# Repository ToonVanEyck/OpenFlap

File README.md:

# OpenFlap

!!! warning

    🚨 This is still a work in progress. Using the the code and files in this repository to create your own display is not recommended at the moment! 🚨

The OpenFlap project aims to create a open source, affordable split-flap display for the makers and tinkerers of the world.
This repository houses all the required files to build, program and modify your very own split-flap display. 

[**Read the Docs**](https://toonvaneyck.github.io/OpenFlap/)

## Specifications

- 48 Flaps per module.
- 49mm x 70mm Character size.
- Stackable & Chainable.
- Daisy chain communication.
- Per module configuration & calibration.
- HTTP API available.
- Modular design.
- 3D printable parts.

## Design Philosophy

The OpenFlap system is designed to be modular and expandable, using common components and manufacturing techniques such as 3D printing and printed circuit boards.

The OpenFlap system uses DC geared motors instead of traditional stepper motors. This simplifies the mechanical design and reduces the cost of the system. Additionally this reduces the power consumption of the system and allows the split-flap display to rotate faster than the traditionally used stepper motors. 

The OpenFlap system is designed to be as plug and play as possible. The system is able to determine it's own display size, and should only require calibration once.

The OpenFlap system has a web interface that allows local control of the display. The web interface uses a HTTP API to communicate with the display, this API also allows external services to communicate with the display. No authentication or security measures are implemented at the moment.

The OpenFlap system can connect to your local WiFi network or host it's own network.

## I want to ...

[... know more about how the OpenFlap system works.](docs/architecture.md)

[... build my own OpenFlap display.](todo)

[... contribute to the OpenFlap project.](docs/developing.md)

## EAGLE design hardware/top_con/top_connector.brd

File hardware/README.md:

Hardware
========

All PCB's are designed in Fusion 360, the source files can be accessed an copied through the links below:

Module
------
### Side Panel
- [side panel: Electronic Design](https://a360.co/3LnqHKp)
- [side panel: PCB](https://a360.co/3OHfgiH)
- [side panel: Schematic](https://a360.co/3EQSoZI)
- [side panel: 3D](https://a360.co/3vO3oD5)

### Flap
- [flap profile: PCB](https://a360.co/3KnExLN)
- [flap profile: 3D](https://a360.co/3KmTDAU)

### Encoder Wheel
- [wheel: PCB](https://a360.co/3LnqMxH)
- [wheel: 3D](https://a360.co/37JMbTs)

Top-Con
-------
- [top-con: Electronic Design](https://a360.co/3KmcPPo)
- [top-con: PCB](https://a360.co/36RFDl1)
- [top-con: Schematic](https://a360.co/3Mybp5H)
- [top-con: 3D](https://a360.co/3ETtb0O)

Controller
----------
- [controller: Electronic Design](https://a360.co/3vmdjzr)
- [controller: PCB](https://a360.co/3LnqmHD)
- [controller: Schematic](https://a360.co/3xTXOSp)
- [controller: 3D](https://a360.co/3rY5W0q)

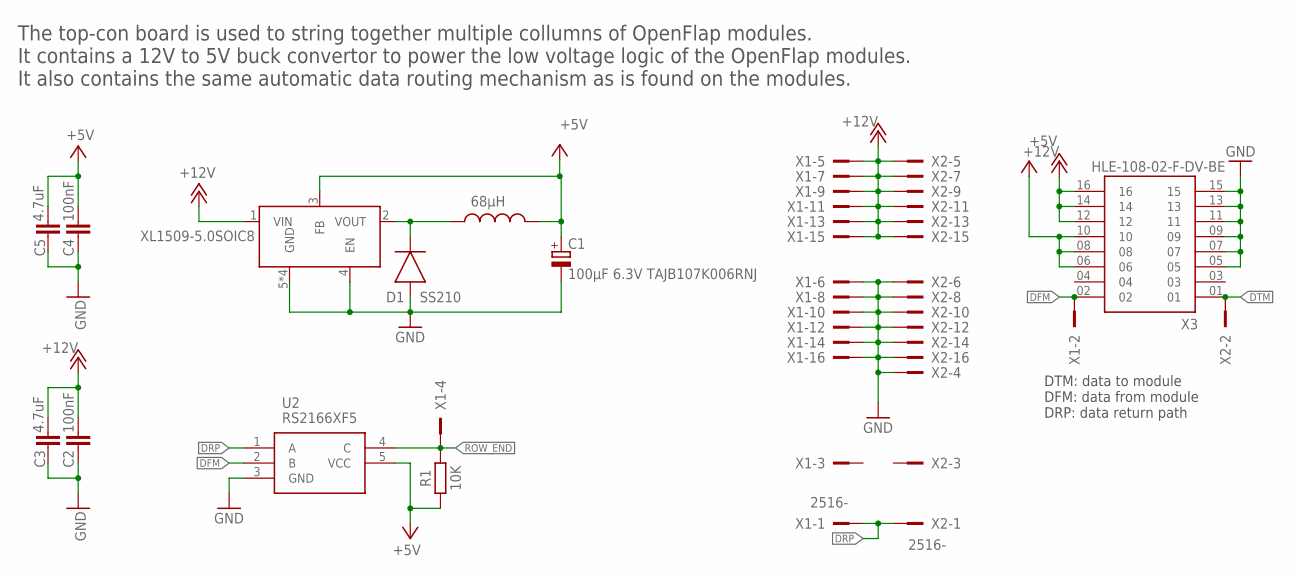
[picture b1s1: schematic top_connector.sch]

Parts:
C1: 100µF 6.3V TAJB107K006RNJ; CAPMP3528X210N
C2, C4: 100nF; CAPC2012X110
C3, C5: 4.7uF; CAPC2012X110
D1: SS210; DIOM5226X290N
L1: SWPA6045S680MT; LVS606028-100M-N
R1: 10K; RESC2012X65
U1: XL1509-5.0SOIC8; SOIC8
U2: RS2166XF5; SOT95P280X145-5N
X1, X2: 2516-; PAK100/2500-16
X3: HLE-108-02-F-DV-BE; SAMTEC_HLE-108-02-F-DV-BE

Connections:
+5V: C1.1 (+), C4.1, C5.1, L1.P$2, R1.1, U1.3 (FB), U2.5 (VCC), X3.06, X3.08, X3.10
+12V: C2.1, C3.1, U1.1 (VIN), X1.5, X1.7, X1.9, X1.11, X1.13, X1.15, X2.5, X2.7, X2.9, X2.11, X2.13, X2.15, X3.12, X3.14, X3.16
DFM: U2.2 (B), X1.2, X3.02
DRP: U2.1 (A), X1.1, X2.1
DTM: X2.2, X3.01
GND: C1.2 (-), C2.2, C3.2, C4.2, C5.2, D1.2 (A), U1.4 (EN), U1.5 (GND), U1.6 (GND), U1.7 (GND), U1.8 (GND), U2.3 (GND), X1.6, X1.8, X1.10, X1.12, X1.14, X1.16, X2.4, X2.6, X2.8, X2.10, X2.12, X2.14, X2.16, X3.05, X3.07, X3.09, X3.11, X3.13, X3.15
unnamed: D1.1 (C), L1.P$1, U1.2 (VOUT)
ROW_END: R1.2, U2.4 (C), X1.4

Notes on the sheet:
DTM: data to module DFM: data from module DRP: data return path
68µH
The top-con board is used to string together multiple collumns of OpenFlap modules. It contains a 12V to 5V buck convertor to power the low voltage logic of the OpenFlap modules. It also contains the same automatic data routing mechanism as is found on the modules.

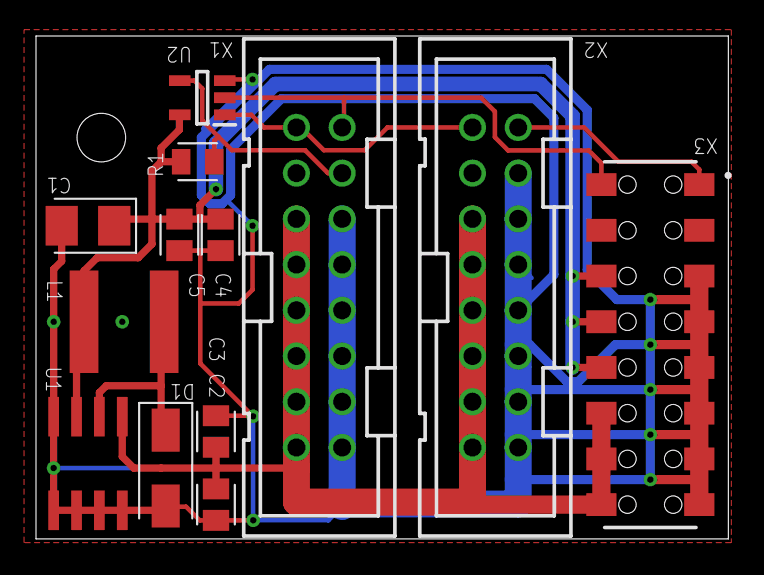
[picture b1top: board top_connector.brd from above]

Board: 2 copper layers, 38.5 x 27.9 mm, 13 parts (0 on the bottom side), 8 nets.

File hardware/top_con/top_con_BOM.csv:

Comment,Designator,Footprint,JLCPCB Part #（optional）
100µF 6.3V TAJB107K006RNJ,C1,C-POL_TANTALUM-1411(3528-METRIC),C16133
100nF,C2,C_CHIP-0805(2012-METRIC),
4.7uF,C3,C_CHIP-0805(2012-METRIC),
100nF,C4,C_CHIP-0805(2012-METRIC),
4.7uF,C5,C_CHIP-0805(2012-METRIC),
SS210,D1,DIODEDO-214AC(SMA),C14996
SWPA6045S680MT,L1,LVS606028-100M-N,C53663
10K,R1,R_CHIP-0805(2012-METRIC),
XL1509-5.0SOIC8,U1,XL1509-5.0SOIC8,C61063
SN74LVC1G66DBVR,U2,SOT23-5,C5375974
2516-,X1,2516-,
2516-,X2,2516-,
HLE-108-02-F-DV-BE,X3,HLE-108-02-F-DV-BE,

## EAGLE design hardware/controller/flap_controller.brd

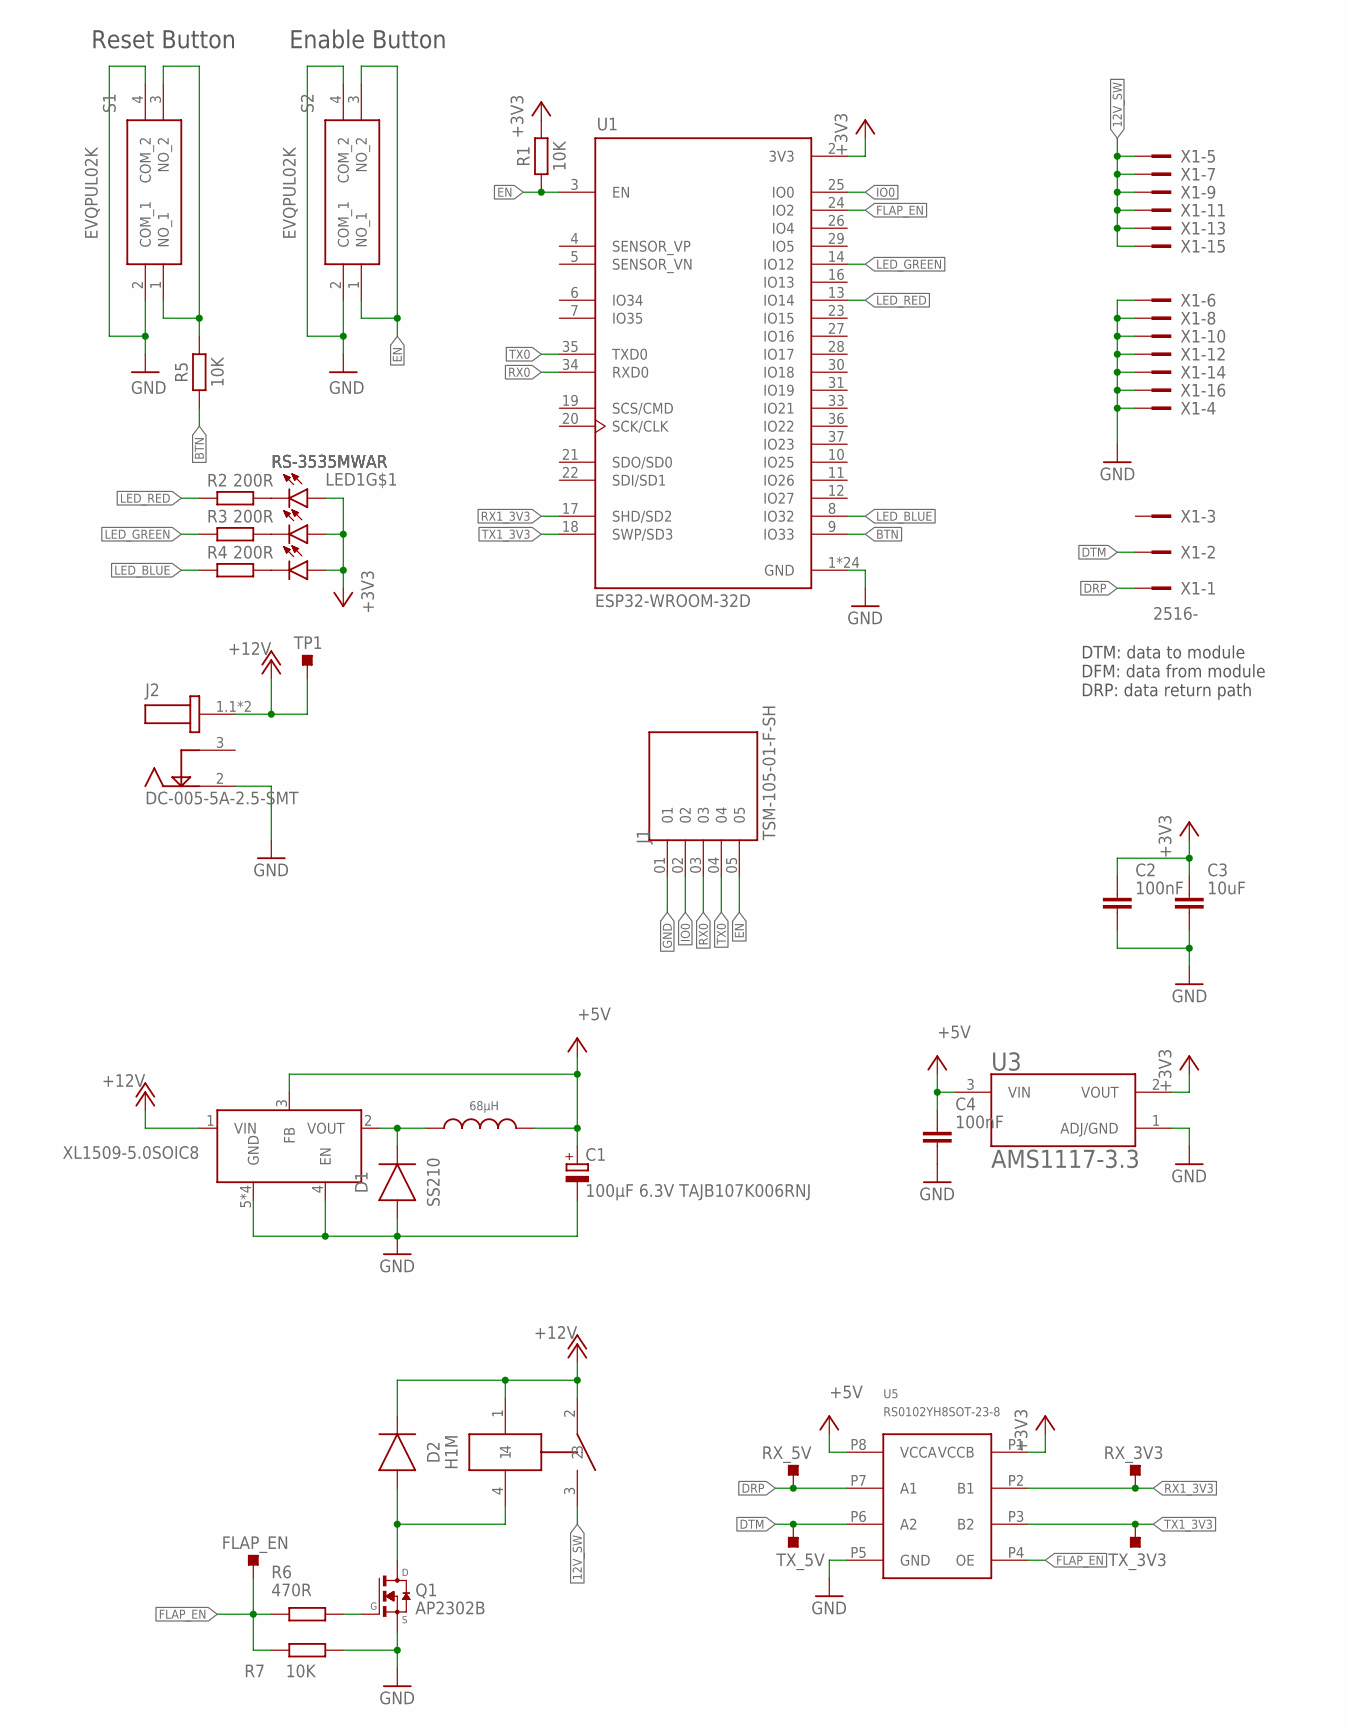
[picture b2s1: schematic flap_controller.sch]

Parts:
C1: 100µF 6.3V TAJB107K006RNJ; CAPMP3528X210N
C2, C4: 100nF; CAPC2012X110
C3: 10uF; CAPC2012X110
D1: SS210; DIOM5226X290N
D2: H1M; SODFL3718X115
FLAP_EN: TESTPOINT_TPS-PAD-036; TESTPOINT_PAD-036
J1: TSM-105-01-F-SH; SAMTEC_TSM-105-01-F-SH
J2: DC-005-5A-2.5-SMT; GCT_DCJ200-05-A-XX-X_REVA
K1: G5NB-1A-E DC12; G5NB-1A-EDC12
L1: SWPA6045S680MT; LVS606028-100M-N
LED1: RS-3535MWAR
Q1: AP2302B; TRANSISTOR-FET_SOT23
R1, R5, R7: 10K; RESC2012X65
R2, R3, R4: 200R; RESC2012X65
R6: 470R; RESC2012X65
RX_3V3, RX_5V: TESTPOINT_TPS-PAD-036; TESTPOINT_PAD-036
S1, S2: EVQPUL02K
TP1: TESTPOINT_TPS-SMD-10SN; TESTPOINT_SMD-10SN
TX_3V3, TX_5V: TESTPOINT_TPS-PAD-036; TESTPOINT_PAD-036
U1: ESP32-WROOM-32D; MODULE_ESP32-WROOM-32D
U2: XL1509-5.0SOIC8; SOIC8
U3: AMS1117-3.3; SOT229P700X180-4N
U5: RS0102YH8SOT-23-8; SOT-23-8
X1: 2516-; PAK100/2500-16

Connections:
12V_SW: K1.3, X1.5, X1.7, X1.9, X1.11, X1.13, X1.15
+3V3: C2.1, C3.1, LED1.B_A (A), LED1.G_A (A), LED1.R_A (A), R1.2, U1.2 (3V3), U3.2 (VOUT), U5.P1 (VCCB)
+5V: C1.1 (+), C4.1, L1.P$2, U2.3 (FB), U3.3 (VIN), U5.P8 (VCCA)
+12V: D2.1 (C), J2.1.1 (1), J2.1.2 (1), K1.1, K1.2, TP1.TP, U2.1 (VIN)
BTN: R5.1, U1.9 (IO33)
DRP: RX_5V.1, U5.P7 (A1), X1.1
DTM: TX_5V.1, U5.P6 (A2), X1.2
EN: J1.05, R1.1, S2.1 (NO_1), S2.3 (NO_2), U1.3 (EN)
FLAP_EN: FLAP_EN.1, R6.1, R7.1, U1.24 (IO2), U5.P4 (OE)
GND: C1.2 (-), C2.2, C3.2, C4.2, D1.2 (A), J1.01, J2.2, Q1.2 (S), R7.2, S1.2 (COM_1), S1.4 (COM_2), S2.2 (COM_1), S2.4 (COM_2), U1.1 (GND), U1.15 (GND), U1.38 (GND), U1.39_1 (GND), U1.39_2 (GND), U1.39_3 (GND), U1.39_4 (GND), U1.39_5 (GND), U1.39_6 (GND), U1.39_7 (GND), U1.39_8 (GND), U1.39_9 (GND), U1.39_10 (GND), U1.39_11 (GND), U1.39_12 (GND), U1.39_13 (GND), U1.39_14 (GND), U1.39_15 (GND), U1.39_16 (GND), U1.39_17 (GND), U1.39_18 (GND), U1.39_19 (GND), U1.39_20 (GND), U1.39_21 (GND), U2.4 (EN), U2.5 (GND), U2.6 (GND), U2.7 (GND), U2.8 (GND), U3.1 (ADJ/GND), U5.P5 (GND), X1.4, X1.6, X1.8, X1.10, X1.12, X1.14, X1.16
IO0: J1.02, U1.25 (IO0)
LED_BLUE: R4.2, U1.8 (IO32)
LED_GREEN: R3.2, U1.14 (IO12)
LED_RED: R2.2, U1.13 (IO14)
unnamed: D1.1 (C), L1.P$1, U2.2 (VOUT)
unnamed: LED1.B_K (C), R2.1
unnamed: LED1.G_K (C), R3.1
unnamed: LED1.R_K (C), R4.1
unnamed: D2.2 (A), K1.4, Q1.3 (D)
unnamed: Q1.1 (G), R6.2
unnamed: R5.2, S1.1 (NO_1), S1.3 (NO_2)
RX0: J1.03, U1.34 (RXD0)
RX1_3V3: RX_3V3.1, U1.17 (SHD/SD2), U5.P2 (B1)
TX0: J1.04, U1.35 (TXD0)
TX1_3V3: TX_3V3.1, U1.18 (SWP/SD3), U5.P3 (B2)

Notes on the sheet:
DTM: data to module DFM: data from module DRP: data return path
Reset Button
68µH
Enable Button

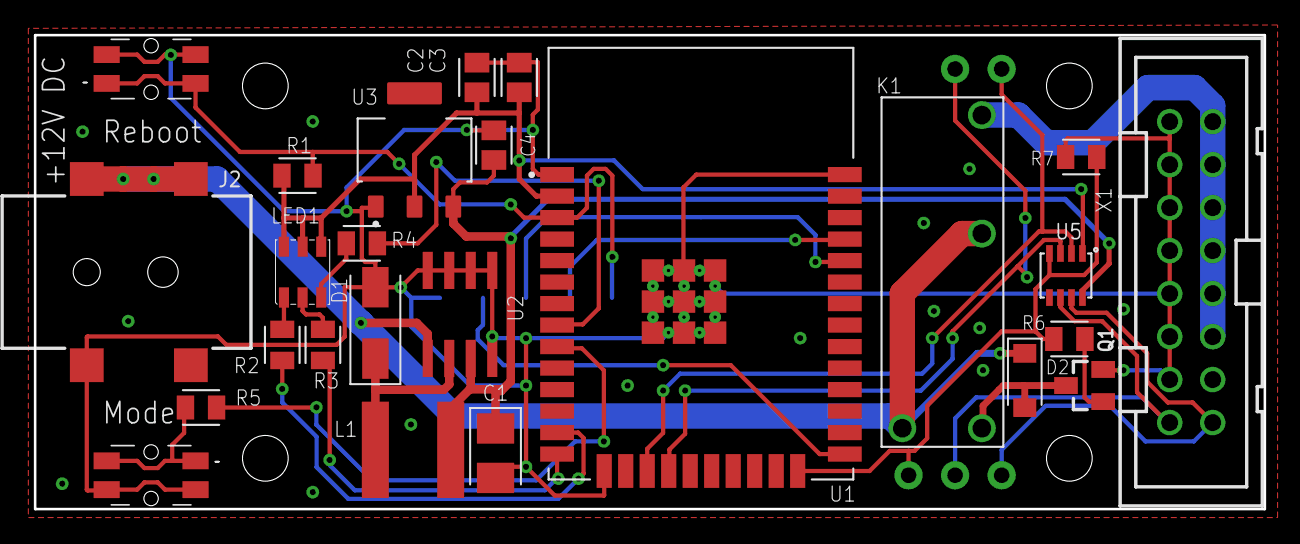
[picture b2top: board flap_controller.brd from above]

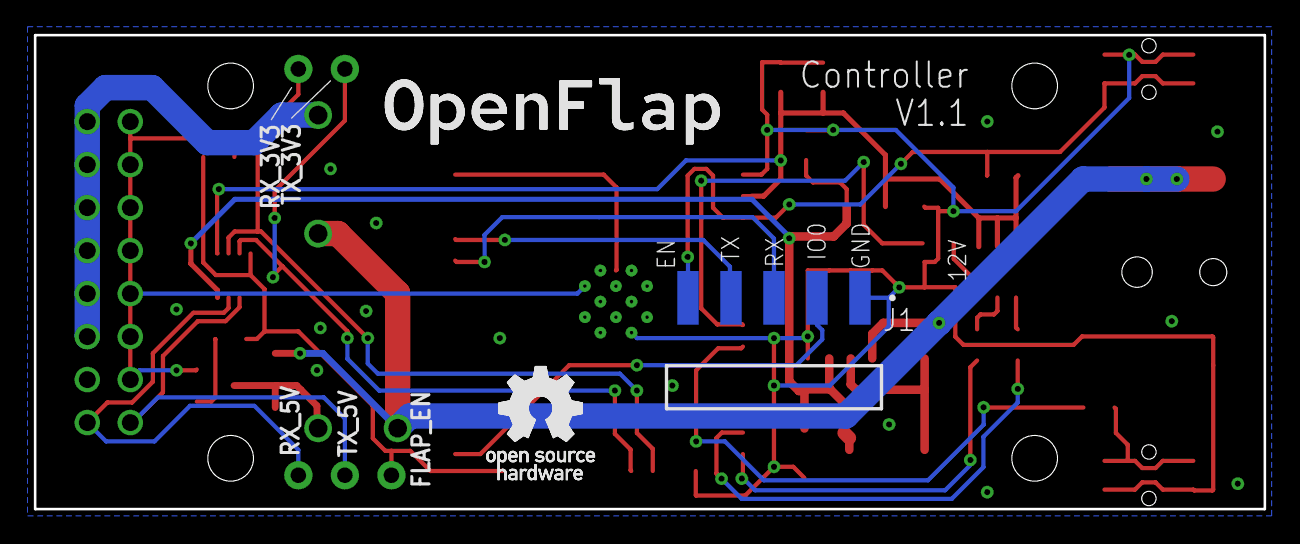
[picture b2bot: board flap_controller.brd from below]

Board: 2 copper layers, 72.6 x 28.0 mm, 32 parts (7 on the bottom side), 25 nets.

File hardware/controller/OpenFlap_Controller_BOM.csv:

Comment,Designator,Footprint,JLCPCB Part #（optional）
100nF,"C2, C4",C_CHIP-0805(2012-METRIC),C49678
TAJB107K006RNJ,C1,C-POL_TANTALUM-1411(3528-METRIC),C16133
10uF,C3,C_CHIP-0805(2012-METRIC),C15850
10K,"R1, R5, R7",R_CHIP-0805(2012-METRIC),C17414
200R,"R2, R3, R4",,C17540
2516-,X1,2516-,C3406
AMS1117-3.3,U3,AMS1117-3.3,C6186
DC-005-5A-2.5-SMT,J2,DCJ200-05-A-XX-X_REVA,C319133
ESP32-WROOM-32D,U1,ESP32-WROOM-32D,C529578
EVQPUL02K,"S1, S2",EVQPUL02K,C79175
G5NB-1A-E DC12,K1,G5NB-1A-EDC12,C225714
RS-3535MWAR,LED1,RS-3535MWAR,C110402
RS0102YH8,U5,RS0102YH8SOT-23-8,C783414
SS210,D1,DIODEDO-214AC(SMA),C14996
SWPA6045S680MT,L1,LVS606028-100M-N,C53663
TSM-105-01-F-SH,J1,TSM-105-01-F-SH,
XL1509-5.0,U2,SOIC8,C2902368
AP2302B,Q1,SOT23,C406812
H1M,D2,SODFL3718X115,C698680

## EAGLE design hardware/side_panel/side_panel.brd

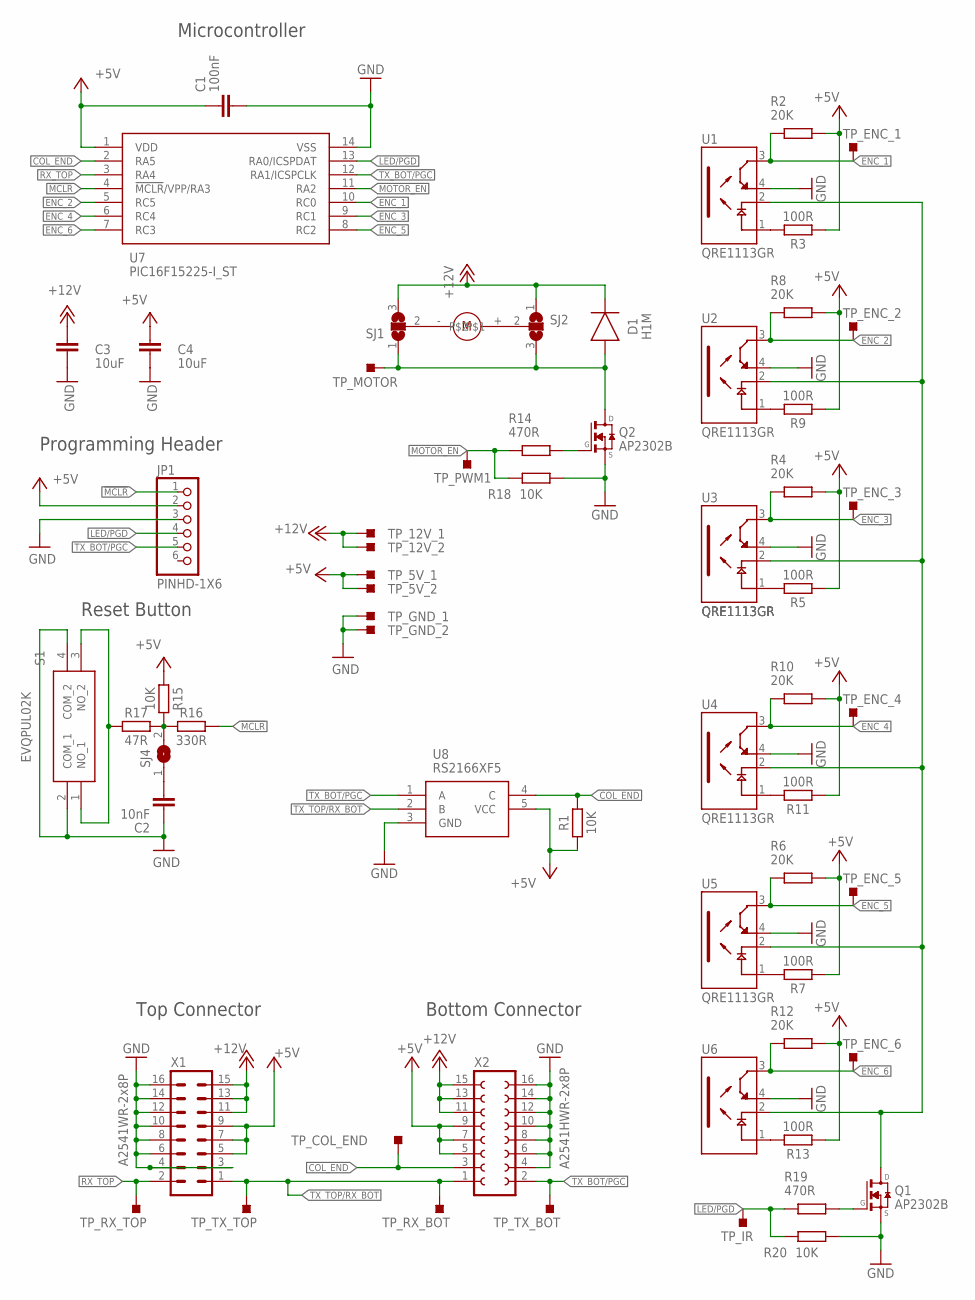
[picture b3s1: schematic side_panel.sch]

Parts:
C1: 100nF; CAPC2012X110
C2: 10nF; CAPC2012X110
C3, C4: 10uF; C0805
D1: H1M; SODFL3718X115
JP1: PINHD-1X6; 1X06
M1: GA12-N20
Q1, Q2: AP2302B; TRANSISTOR-FET_SOT23
R1, R15, R18, R20: 10K; RESC2012X65
R2, R4, R6, R8, R10, R12: 20K; RESC2012X65
R3, R5, R7, R9, R11, R13: 100R; RESC2012X65
R14, R19: 470R; RESC2012X65
R16: 330R; RESC2012X65
R17: 47R; RESC2012X65
S1: EVQPUL02K
SJ1, SJ2: SJ2W; SJ_2
SJ4: SJ
TP_5V_1, TP_5V_2, TP_12V_1, TP_12V_2: TESTPOINT_TPS-PAD-036; TESTPOINT_PAD-036
TP_COL_END: TESTPOINT_TPS-PAD-036; TESTPOINT_PAD-036
TP_ENC_1, TP_ENC_2, TP_ENC_3, TP_ENC_4, TP_ENC_5, TP_ENC_6: TESTPOINT_TPS-PAD-036; TESTPOINT_PAD-036
TP_GND_1, TP_GND_2: TESTPOINT_TPS-PAD-036; TESTPOINT_PAD-036
TP_IR: TESTPOINT_TPS-PAD-036; TESTPOINT_PAD-036
TP_MOTOR: TESTPOINT_TPS-PAD-036; TESTPOINT_PAD-036
TP_PWM1: TESTPOINT_TPS-PAD-036; TESTPOINT_PAD-036
TP_RX_BOT: TESTPOINT_TPS-PAD-036; TESTPOINT_PAD-036
TP_RX_TOP: TESTPOINT_TPS-PAD-036; TESTPOINT_PAD-036
TP_TX_BOT: TESTPOINT_TPS-PAD-036; TESTPOINT_PAD-036
TP_TX_TOP: TESTPOINT_TPS-PAD-036; TESTPOINT_PAD-036
U1, U2, U3, U4, U5, U6: QRE1113GR; SOIC180P460X187-4N
U7: PIC16F15225-I_ST; SOP65P640X120-14N
U8: RS2166XF5; SOT95P280X145-5N
X1: A2541WR-2x8P; MA08-2W
X2: A2541HWR-2x8P; FE08-2W

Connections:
!MCLR: JP1.1, R16.2, U7.4 (!MCLR!/VPP/RA3)
+5V: C1.1, C4.1, JP1.2, R1.1, R2.2, R3.1, R4.2, R5.1, R6.2, R7.1, R8.2, R9.1, R10.2, R11.1, R12.2, R13.1, R15.1, TP_5V_1.1, TP_5V_2.1, U7.1 (VDD), U8.5 (VCC), X1.5, X1.7, X1.9, X2.5, X2.7, X2.9
+12V: C3.1, D1.1 (C), SJ1.3, SJ2.1, TP_12V_1.1, TP_12V_2.1, X1.11, X1.13, X1.15, X2.11, X2.13, X2.15
COL_END: R1.2, TP_COL_END.1, U7.2 (RA5), U8.4 (C), X2.3
ENC_1: R2.1, TP_ENC_1.1, U1.3 (CT), U7.10 (RC0)
ENC_2: R8.1, TP_ENC_2.1, U2.3 (CT), U7.5 (RC5)
ENC_3: R4.1, TP_ENC_3.1, U3.3 (CT), U7.9 (RC1)
ENC_4: R10.1, TP_ENC_4.1, U4.3 (CT), U7.6 (RC4)
ENC_5: R6.1, TP_ENC_5.1, U5.3 (CT), U7.8 (RC2)
ENC_6: R12.1, TP_ENC_6.1, U6.3 (CT), U7.7 (RC3)
GND: C1.2, C2.1, C3.2, C4.2, JP1.3, Q1.2 (S), Q2.2 (S), R18.2, R20.2, S1.2 (COM_1), S1.4 (COM_2), TP_GND_1.1, TP_GND_2.1, U1.4 (ET), U2.4 (ET), U3.4 (ET), U4.4 (ET), U5.4 (ET), U6.4 (ET), U7.14 (VSS), U8.3 (GND), X1.3, X1.4, X1.6, X1.8, X1.10, X1.12, X1.14, X1.16, X2.4, X2.6, X2.8, X2.10, X2.12, X2.14, X2.16
LED/PGD: JP1.4, R19.1, R20.1, TP_IR.1, U7.13 (RA0/ICSPDAT)
MOTOR_EN: R14.1, R18.1, TP_PWM1.1, U7.11 (RA2)
unnamed: M1.-, SJ1.2
unnamed: M1.+, SJ2.2
unnamed: D1.2 (A), Q2.3 (D), SJ1.1, SJ2.3, TP_MOTOR.1
unnamed: R3.2, U1.1 (A)
unnamed: Q2.1 (G), R14.2
unnamed: R5.2, U3.1 (A)
unnamed: Q1.3 (D), U1.2 (C), U2.2 (C), U3.2 (C), U4.2 (C), U5.2 (C), U6.2 (C)
unnamed: R7.2, U5.1 (A)
unnamed: Q1.1 (G), R19.2
unnamed: R9.2, U2.1 (A)
unnamed: R11.2, U4.1 (A)
unnamed: R13.2, U6.1 (A)
unnamed: C2.2, SJ4.1
unnamed: R15.2, R16.1, R17.2, SJ4.2
unnamed: R17.1, S1.1 (NO_1), S1.3 (NO_2)
RX_TOP: TP_RX_TOP.1, U7.3 (RA4), X1.2
TX_BOT/PGC: JP1.5, TP_TX_BOT.1, U7.12 (RA1/ICSPCLK), U8.1 (A), X2.2
TX_TOP/RX_BOT: TP_RX_BOT.1, TP_TX_TOP.1, U8.2 (B), X1.1, X2.1

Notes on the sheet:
Top Connector
Bottom Connector
Reset Button
Programming Header
Microcontroller

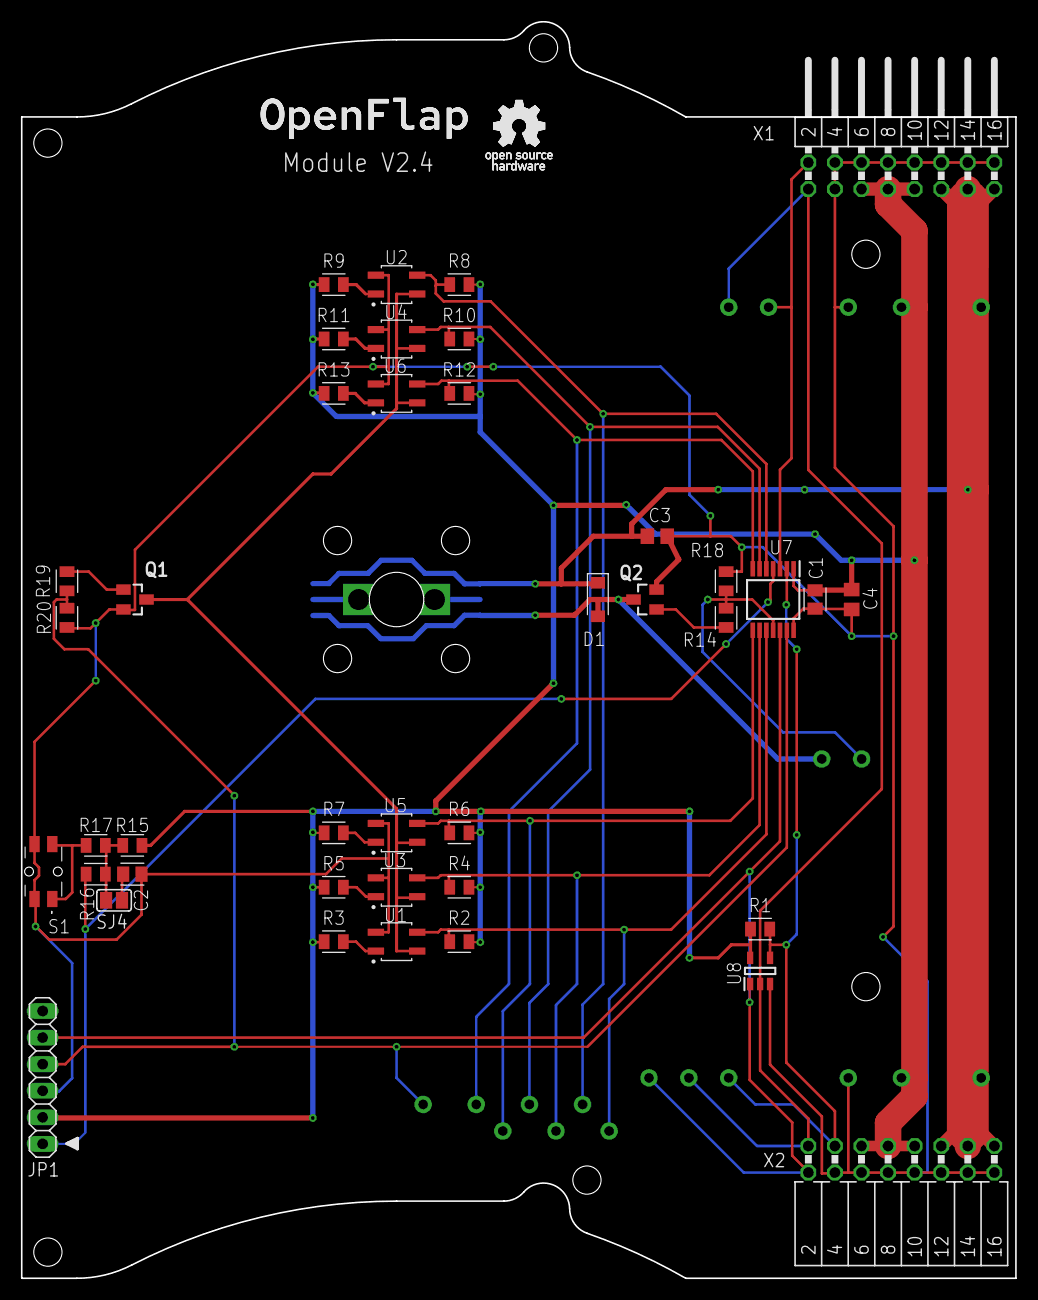
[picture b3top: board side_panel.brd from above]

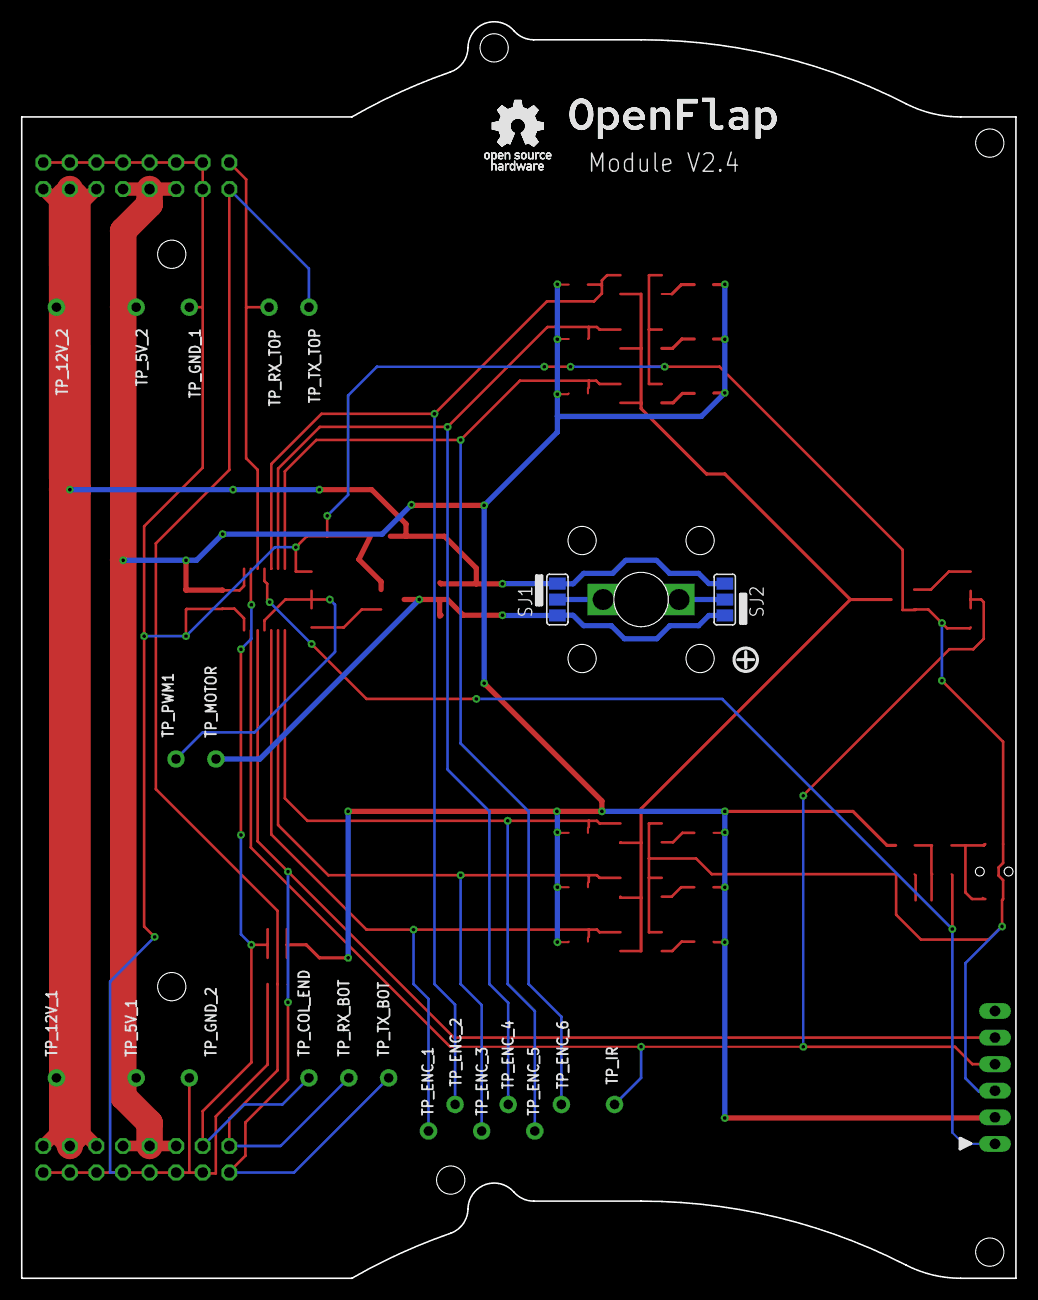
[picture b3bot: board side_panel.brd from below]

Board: 2 copper layers, 95.0 x 120.1 mm, 63 parts (14 on the bottom side), 31 nets.

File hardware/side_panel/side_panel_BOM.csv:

Comment,Designator,Footprint,JLCPCB Part #（optional）
100nF,C1,CAPC2012X110,
10nF,C2,CAPC2012X110,
10uF,C3,C15850,
10uF,C4,C15850,
H1M,D1,SODFL3718X115,C698680
PINHD-1X6,JP1,1X06,
GA12-N20,M1,GA12-N20,
AP2302B,Q1,TRANSISTOR-FET_SOT23,C406812
AP2302B,Q2,TRANSISTOR-FET_SOT23,C406812
10K,R1,RESC2012X65,
20K,R2,RESC2012X65,
100R,R3,RESC2012X65,
20K,R4,RESC2012X65,
100R,R5,RESC2012X65,
20K,R6,RESC2012X65,
100R,R7,RESC2012X65,
20K,R8,RESC2012X65,
100R,R9,RESC2012X65,
20K,R10,RESC2012X65,
100R,R11,RESC2012X65,
20K,R12,RESC2012X65,
100R,R13,RESC2012X65,
470R,R14,RESC2012X65,
10K,R15,RESC2012X65,
330R,R16,RESC2012X65,
47R,R17,RESC2012X65,
10K,R18,RESC2012X65,
470R,R19,RESC2012X65,
10K,R20,RESC2012X65,
EVQPUL02K,S1,EVQPUL02K,C79175
QRE1113GR,U1,SOIC180P460X187-4N,C232862
QRE1113GR,U2,SOIC180P460X187-4N,C232862
QRE1113GR,U3,SOIC180P460X187-4N,C232862
QRE1113GR,U4,SOIC180P460X187-4N,C232862
QRE1113GR,U5,SOIC180P460X187-4N,C232862
QRE1113GR,U6,SOIC180P460X187-4N,C232862
PIC16F15225-I_ST,U7,SOP65P640X120-14N,C3237661
SN74LVC1G66DBVR,U8,SOT23-5,C5375974
A2541WR-2x8P,X1,MA08-2W,C239339
A2541HWR-2x8P,X2,FE08-2W,C239359

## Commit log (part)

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2022-04-25 Fixed typo
2022-04-25 added uart protocol description to README.md
2022-04-25 added 3d printing mesh files for modules
2022-04-25 changed 3mf files to stl files for better support on github.
2022-04-27 updated wiring svg
2022-04-27 replaced wiring diagram with by png
2022-04-27 Added linkes to 3d designs and pcb designs
2022-04-28 Added POC video
2022-05-02 Converted the old websocket based interface to a proper REST api.
2022-05-03 fixed bug causing corruped encoder offsets in modules
2022-05-03 Cleanup of encoder reading in module code
2022-05-03 tweeked pwm table to account for chnage from 100rpm to 60 rpm motor
2022-05-03 Fixed module initialization so the don't start on boot.
2022-05-05 Added script and other resources for procedurally generating flap PCB production files (gerbers) with inkscape and eagle.
2022-05-09 updated gitignore
2022-05-12 Added production files for controller, top-con and flap.
2022-05-13 Some code cleanup work
2022-05-13 Added module production files
2022-05-16 added statistics api with revolution counter but disabled the volatile storage for the rev counter.
2022-05-16 store revolution counter in nvm
2022-05-17 implemented a more complete version api. vesrion is shown as generated by ```git describe --tags --dirty=*```
2022-05-23 fixed issue in web page caused by scrollbar
2022-05-24 fixed issue in webpage caused by typo and some cleanup
2022-05-24 major cleanup/rework of module firmware. The firmware now executes at fixed tick rate of 10kHz
2022-05-24 fixed issue in cmake firmware version generation
2022-05-24 Fixed proper initialization of webpage through api calls. Added loader indicator.
2022-05-26 Added vtrim command and added increment and decrement mode to offset. No support for controller yet.
2022-05-31 reactivated revolution counter
2023-01-06 Added support for doing a complete revolution by sending a newline character.
2023-01-06 UI improvements
2023-01-06 Updated controller api to include vtrim en offset getters and removed statistics api
2023-06-27 Major rework of the controller and module communication. Rework of webpage. Reworked module properties.
2023-07-15 Added a devcontainer supporting ESP-IDF 5.1. Fixed a bug in the offset and vtrim module view.
2023-07-15 Add back removed files
2023-07-22 added eagle schematics and boards
2023-07-25 Updated the flap generations scripts to provide better gerber files for JLCPCB, ToDo: generate new flaps.
2023-07-25 Added new flap PCB production files
2023-08-02 Redrawn the 3d printed parts.
2023-08-02 Updated top-con board to use only one screw and improved the screw location
2023-09-13 Fix: Setting character map entries was broken.
2023-09-20 Fixed bug in json respons from controller
2024-03-21 started porting to py32f003 based module
2024-03-27 finished chaincomm FSM
2024-03-29 Added property handlers
2024-03-31 minor fixes
2024-04-04 fixed chaincomm and flash storage
2024-04-05 Added default configuration
2024-04-14 update cmake structure
2024-04-14 add addresses to flash functions
2024-04-20 Start work on bootloader
2024-04-22 implement jump to app function
2024-04-26 improved bootloader
2024-04-30 fix broken interrupts in app because of bootloader
2024-05-07 removed PIC firmware, module will use an ARM
2024-06-02 intermediate commit, working on ota
2024-06-08 Fixed bootloader
2024-06-09 add ir sensor adc calibration over rtt
2024-06-19 Fixed issues with the communication protocol and added random IR sensor offset and random seed generation.
2024-07-21 major rework of the communication and uart driver
2024-07-23 disable RTT debugging while communications a re ongoing as they might prevent the uart interrupt
2024-07-27 Switching to KiCad: Added top connector schematic and board
2024-08-19 initial commit: work in progress
2024-08-20 update flap template
2024-08-20 add flap destructor
2024-08-20 Add support for exporting and loading project as json. Redesign frontend using bootstrap (WIP)
2024-09-05 create default set and readme
2024-09-05 replace old flap dir with v2
2024-09-05 Add screenshot of flap generator
2024-09-05 Minor fixes to flap generator
2024-09-06 add workflow for generating pdf's from schematic
2024-09-06 test pr
2024-09-06 Workflow: Generate KiCad files
2024-09-11 splitting devcontainers, added devcontainer for kibot testing
2024-09-14 split devcontainer into 3 containers
2024-09-16 Use kibot on sidepanel and top connector
2024-09-20 set fetch depth in workflow
2024-09-21 Fix workflow
2024-09-25 fix typos
2024-10-03 Add FreeCad model and update board layout.
2024-10-03 install git lfs ind evcontainers
2024-10-11 Add script to exptort stl files from freecad
2024-10-16 Add workflow for validating Freecad Design
2024-10-16 enable lfs in github action
2024-10-16 make build dir
2024-10-18 Add support for directional motor control and braking
2024-10-18 tune default ramp
2024-10-22 improved core printability
2024-10-22 update puya docker
2024-10-22 add support for minimum rotation distance
2024-10-22 update gerbolyzer ci script to build out of source
2024-10-23 create encoder wheel in kicad
2024-12-27 Remade controller hardware in KiCad.
2024-12-28 Added TVS diode to UART line on side pannel
2024-12-28 Changed micro symbol to uF
2024-12-29 ad bash completion to kibot container
2024-12-29 hardware/resources/DC_JACK_SMT.stp: convert to Git LFS
2024-12-29 add a case for the controller
2024-12-30 added blender renderes to kibot
2025-01-01 Updated controller footprint and added testpads
2025-01-01 Added LCSC part number for esp32
2025-01-10 docs/images/browser_based_flap_generator.png,docs/images/controller.png,docs/images/flap_assembler.png,docs/images/flap_controller.png,docs/images/module.png,docs/images/signalpath.png,docs/images/to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
2025-01-16 Make FreeCad CI script callable from root
2025-01-16 rename some vars in ci script
2025-01-16 offset encoder pattern so inner trace does not line up with fasteners
2025-01-16 reverse motor polarity on side pannel
2025-01-16 add option to only run the kicad ci script for modified boards.
2025-01-16 added oled_disp component
2025-01-16 Added support for OLED display
2025-01-16 wip oled stuff
2025-01-16 experimenting with testing
2025-01-16 refactor: improve error handling and update message structures in chain communication
2025-01-16 change permissions
2025-01-16 attempt at compile time handler registration with linker fragment section
2025-01-16 fix resize bug causing crashes when resizing to zero
2025-01-16 Bring webserver up to date to switch to new api format
2025-01-16 add beginnings of controller OTA
2025-01-16 implemented writing dynamic length properties and fixed bug in rbuff
2025-01-21 Implement exporting of flap svg to stl file.
2025-01-21 remove magic numbers
2025-01-24 increase color thickness on 3d printed flaps
2025-01-24 remove print statements
2025-01-25 Fix position of characters which do not touch top edge of flap.
2025-01-26 fix: flip front and back of 3d printed flaps
2025-01-28 update side panel schematic motor RPM
2025-01-28 docs: add doc for running devcontainers using devcontainer cli
2025-01-29 reduce flap wheel side to side tolerance
2025-02-01 finish chain com module ota
2025-02-01 Add support for WriteSeq chain com command
2025-02-01 check display size when uploading module firmware
2025-02-01 finish up module OTA
2025-02-01 fix chain com read all dynamic size not working for consecutive modules
2025-02-01 start implementing firmware property for module ota
2025-02-01 add debug pin wiggling to side pannel
2025-02-01 Add short backspin to align lock flap against the latch.
2025-02-02 shrink top 0.5mm and reduce retainer thickness by .25mm
2025-02-02 minor tweaks
2025-02-02 rename controller_v2 to controller
2025-02-02 improved ir encoder response time
2025-02-03 remove test file
2025-02-03 update github actions for new devcontainers
2025-02-03 add mdns support
2025-02-09 encoder changes
2025-02-10 changed hole patern encoder wheel
2025-02-11 update pcb model in cad design
2025-02-12 rework properties wip
2025-02-15 added properties to controller (untested)
2025-02-18 Increase encoder LED current to 70mA and make make two pairs of 3 to reduce power draw
2025-02-27 fix pipeline
2025-02-28 Update github actions
2025-03-03 Setup formatting and codespell
2025-03-06 Update openflap module to use incremental encoder
2025-03-07 change latch position and geometry
2025-03-07 Side panel 5.0.1 swap motor polarity
2025-03-08 Start homing on boot and prevent flippering between 1 and 0.
2025-03-09 working on docs
2025-03-12 Fixed reworked properties
2025-03-26 Rework controller webpage for setting module properties
2025-03-27 increase hub and core CAD tolerances to reduce friction
2025-03-27 Add motor mode with breaking in order to slow down
2025-03-29 Fix module startup calibration.
2025-03-29 fix, send reboot command after module OTA in proper sequence
2025-03-29 update top connector to improve current path
2025-04-25 Add french cleat mounting system
2025-04-25 Fix broken flap to 3d script
2025-04-27 sepper 4 step
2025-04-27 stepper experiments
2025-04-28 Change CAD design to work with 35mm stepper motor
2025-05-17 Create proper stepper driver.
2025-07-10 Add simple ota script to bulk update the modules and provide immediate feedback based on CRC matching
2025-07-23 Implemented position pid, but considering speed pid instead...
2025-07-31 Rework top connector and side panel connections to increase power rating. Switch from 2 channel to 4 channel incremental encoder.
2025-08-02 Update side panel to add proper ESD protection, 12V detection, removed uart switch in favor of software switching, shuffled around some IO for improved routing.
2025-08-02 Reduced PWM frequency decrease switching losses in h-bride.
2025-08-23 side panel v7
2025-08-27 rework sidepanel to 3 sensors, ad 12V ok signal, add debug uart, change test points for skedd connector
2025-09-01 Fixed OTA, Added checksum to chain comm
2025-09-08 Change idle motor state from brake to freewheel to reduce power consumption.
2025-09-08 Optimize flap latch shape.
2025-09-15 Fix synchronization issue between controller and modules
2025-09-15 Update OTA ui logic
2025-09-16 Added logger to web UI but it's jank because I suck at html & css
2025-09-16 Fix issue causing calibration not to got to home position.
2025-09-17 fix bug in controller api handlers
2025-09-22 Design controller as a top connector board.
2025-09-23 fix erroneous U4 angle from 45 to 37.5
2025-09-24 rename function
2025-09-24 update output files of hardware
2025-09-27 Documentation Updates
2025-09-28 Add Flap Generator docs
2025-09-29 Update Github Pages to docs
2025-10-03 super basic one node test working for read all
2025-10-03 implement single node test for all 3 chain comm actions
2025-10-07 Add RO and WO tests
2025-10-07 Add timeout tests
2025-10-08 Start on rev2 chain com
2025-10-09 Finish Read V2
2025-10-09 Implement proper RX_HEADER state test
2025-10-15 Change firmware HAL for V7 hardware
2025-10-15 Complete Redesign of Chain Communication Protocol
2025-10-16 Fixed compile errors in master but it's still shit.
2025-10-21 Port firmware version, update and command property to new implementation.
2025-10-22 Ported all property handlers, untested
2025-10-23 Add motor control safety check for 12V power supply
2025-11-03 Reverse payload order when writing
2025-11-04 Enhance chain communication with queuing mechanism and UART callbacks
    - Added queuing support for read and write actions in the chain communication master.
    - Introduced UART callback for waiting until transmission is complete.
    - Updated synchronization logic to handle retries for property synchronization.
    - Adjusted timeout values for improved responsiveness.
    - Enhanced error logging for better debugging of module errors.
2025-11-04 Implement WRITE to BROADCAST updating
2025-11-06 Fix return codes of module prop handlers
2025-11-10 Update power specifications and connector type in architecture and controller documentation
2025-11-12 Renamed "chain comm" to "madelink" and made it into a submodule
2026-05-27 Fix erroneous offset_delta calculation for offset calibration.
2026-05-27 Update note in schematic
2026-06-16 fix: V-001 security vulnerability
    Automated security fix generated by OrbisAI Security
